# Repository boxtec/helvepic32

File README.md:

# HelvePic32
HelvePic32 Kit

See http://helvepic32.net or http://helvepic32.org/ for more information.

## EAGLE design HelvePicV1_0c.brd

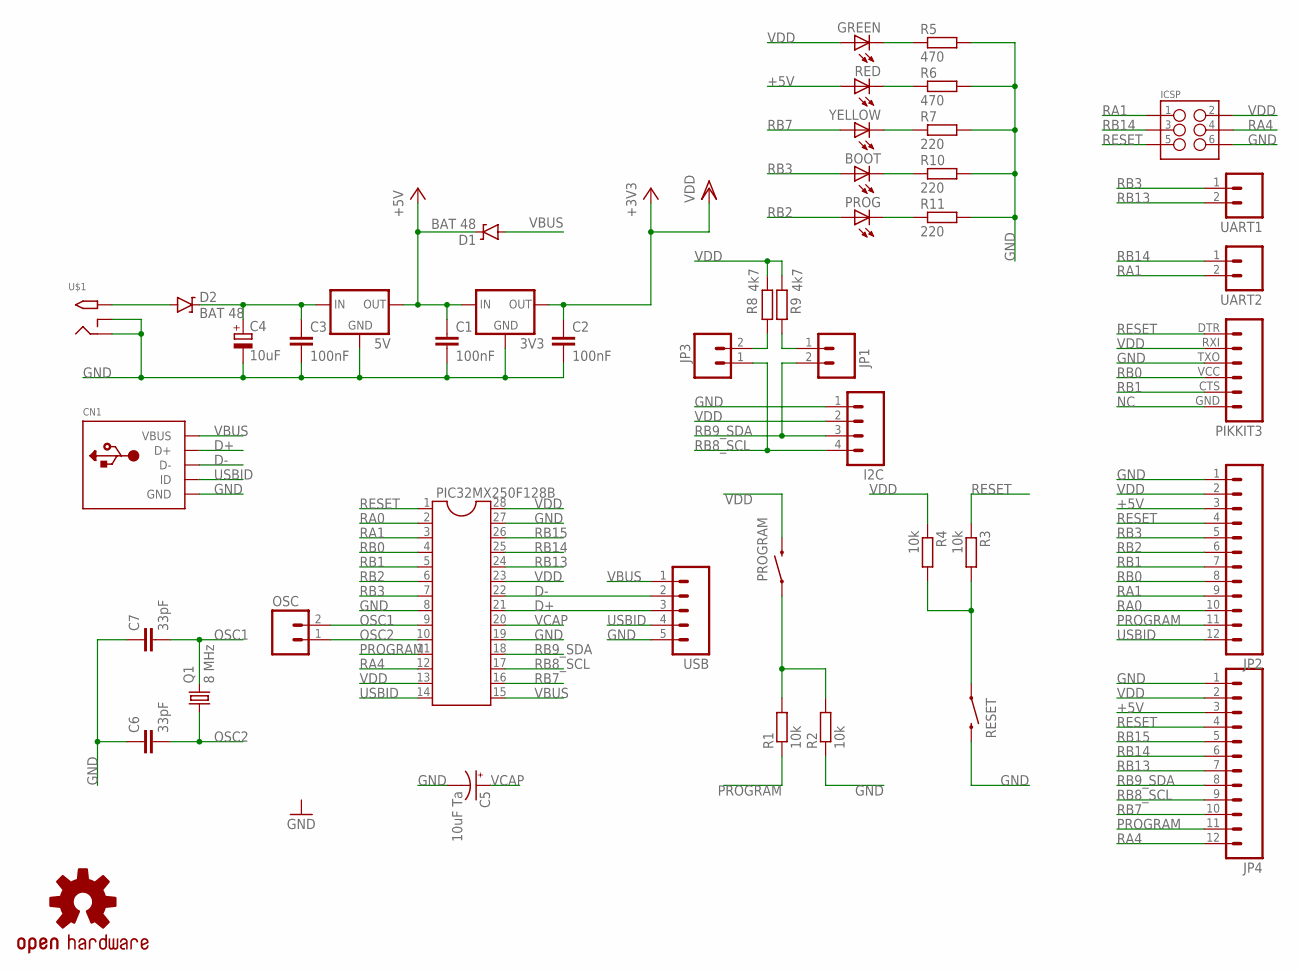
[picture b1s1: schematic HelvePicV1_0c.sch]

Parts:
3V3, 5V: MCP1700INLINE; TO92-INLINE
BOOT: LED3MM
C1, C2, C3: 100nF; C025-030X050
C4: 10uF; E5-6
C5: 10uF Ta; CPOL-RADIAL-10UF-25V
C6, C7: 33pF; C025-030X050
CN1: USBMOLEX; USB-MINIB-THM-MOLEX
D1, D2: BAT 48; DIODE-ZENER
GREEN: LED3MM
I2C: M04PTH; 1X04
ICSP: M03X22X3_SILK_SM; 2X3
JP1, JP3: M02PTH; 1X02
JP2, JP4: M12PTH; 1X12
LOGO1: OSHW-LOGOS; OSHW-LOGO-S
OSC: M02PTH; 1X02
PIC32MX250F128B: DIL28-3
PIKKIT3: M06SIP; 1X06
PROG: LED3MM
PROGRAM: SWITCH-MOMENTARY-2PTH; TACTILE-PTH
Q1: 8 MHz; HC49U-V
R1, R2, R3, R4: 10k; 0207/7
R5, R6: 470; 0207/7
R7, R10, R11: 220; 0207/7
R8, R9: 4k7; 0207/7
RED: LED3MM
RESET: SWITCH-MOMENTARY-2PTH; TACTILE-PTH
U$1: 2.1MMJACKTHM; PJ-102A
UART1, UART2: M02PTH; 1X02
USB: M05PTH; 1X05
YELLOW: LED3MM

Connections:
+5V: 3V3.2 (IN), 5V.3 (OUT), C1.1, D1.P$1 (C), JP2.3, JP4.3, RED.A
D+: CN1.D+, PIC32MX250F128B.21, USB.3
D-: CN1.D-, PIC32MX250F128B.22, USB.2
GND: 3V3.1 (GND), 5V.1 (GND), C1.2, C2.2, C3.2, C4.-, C5.2 (-), C6.1, C7.1, CN1.GND, I2C.1, ICSP.6, JP2.1, JP4.1, PIC32MX250F128B.8, PIC32MX250F128B.19, PIC32MX250F128B.27, PIKKIT3.TXO (3), R2.1, R5.2, R6.2, R7.2, R10.2, R11.2, RESET.3 (2), U$1.RING, U$1.RING_SW, USB.5
unnamed: JP3.2, R8.2
unnamed: GREEN.K (C), R5.1
unnamed: R6.1, RED.K (C)
unnamed: JP1.1, R9.2
unnamed: D2.P$2 (A), U$1.TIP
unnamed: 5V.2 (IN), C3.1, C4.+, D2.P$1 (C)
unnamed: PROGRAM.1, R1.2, R2.2
unnamed: R3.2, R4.2, RESET.1
NC: PIKKIT3.GND (6)
OSC1: C7.2, OSC.2, PIC32MX250F128B.9, Q1.2
OSC2: C6.2, OSC.1, PIC32MX250F128B.10, Q1.1
PROGRAM: JP2.11, JP4.11, PIC32MX250F128B.11, R1.1
RA0: JP2.10, PIC32MX250F128B.2
RA1: ICSP.1, JP2.9, PIC32MX250F128B.3, UART2.2
RA4: ICSP.4, JP4.12, PIC32MX250F128B.12
RB0: JP2.8, PIC32MX250F128B.4, PIKKIT3.VCC (4)
RB1: JP2.7, PIC32MX250F128B.5, PIKKIT3.CTS (5)
RB2: JP2.6, PIC32MX250F128B.6, PROG.A
RB3: BOOT.A, JP2.5, PIC32MX250F128B.7, UART1.1
RB7: JP4.10, PIC32MX250F128B.16, YELLOW.A
RB8_SCL: I2C.4, JP3.1, JP4.9, PIC32MX250F128B.17
RB9_SDA: I2C.3, JP1.2, JP4.8, PIC32MX250F128B.18
RB13: JP4.7, PIC32MX250F128B.24, UART1.2
RB14: ICSP.3, JP4.6, PIC32MX250F128B.25, UART2.1
RB15: JP4.5, PIC32MX250F128B.26
RESET: ICSP.5, JP2.4, JP4.4, PIC32MX250F128B.1, PIKKIT3.DTR (1), R3.1
USBID: CN1.ID, JP2.12, PIC32MX250F128B.14, USB.4
VBUS: CN1.VBUS, D1.P$2 (A), PIC32MX250F128B.15, USB.1
VCAP: C5.1 (+), PIC32MX250F128B.20
VDD: 3V3.3 (OUT), C2.1, GREEN.A, I2C.2, ICSP.2, JP2.2, JP4.2, PIC32MX250F128B.13, PIC32MX250F128B.23, PIC32MX250F128B.28, PIKKIT3.RXI (2), PROGRAM.3 (2), R4.1, R8.1, R9.1
YELLOW: R7.1, YELLOW.K (C)
YELLOW1: BOOT.K (C), R10.1
YELLOW2: PROG.K (C), R11.1

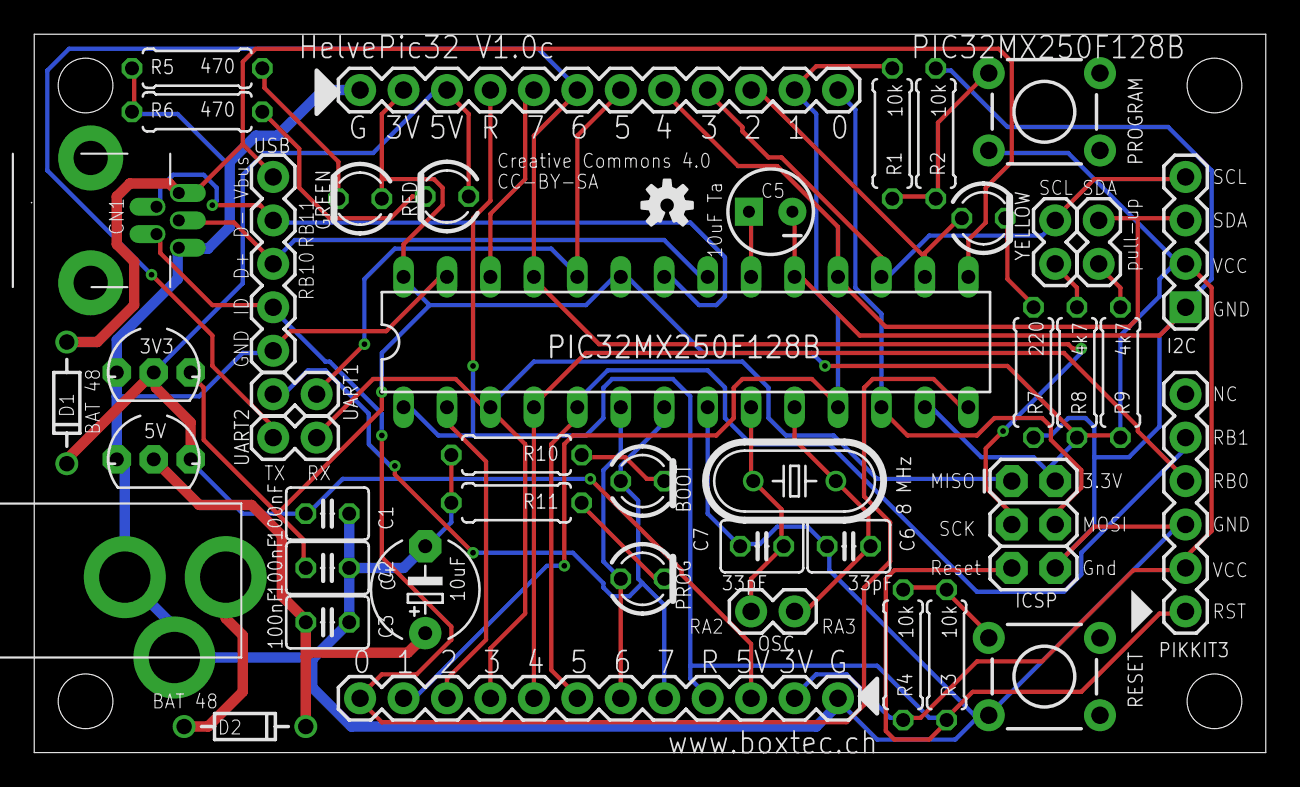
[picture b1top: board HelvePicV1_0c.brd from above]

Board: 2 copper layers, 72.0 x 42.0 mm, 45 parts (0 on the bottom side), 36 nets.

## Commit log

2015-09-10 Initial git import

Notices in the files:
HelvePicV1_0c.brd:
Creative Commons 4.0
CC-BY-SA
parts and their libraries:
SparkFun-Capacitors: Licensing: Creative Commons ShareAlike 4.0 International - https://creativecommons.org/licenses/by-sa/4.0
